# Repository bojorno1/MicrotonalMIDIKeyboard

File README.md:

<h1>Microtonal MIDI Keyboard</h1>

<h2><em>the notes between the notes...</em></h2>
<br>
This is a microtonal MIDI keyboard, made for the Hack Club Half-Life project week 3/8.
<br>
This keyboard adds extra keys for the keys C 1/4#, C 3/4#, D 1/4#, D 3/4#, and so on. This keyboard uses low-profile MX keys as its switches, which are set in a matrix as to save IO on the Waveshare ESP32-S3-Zero. There is also a rotary encoder present on the board for volume control and mute functions. Special keycaps for this board will be 3D-Printable and found in the Keycaps folder in this repository once created. This keyboard uses MIDI 1.0 to transmit the musical data from this keyboard. Please note that the data used for microtones in this keyboard may not be compatible with certain softwares.
<br>
Set up instructions will be available upon firmware completion. 
<h4>Schematics available <a href="https://github.com/bojorno1/MicrotonalMIDIKeyboard/blob/main/pcb/schematic.pdf">here...</a></h4>
<h4>Keycap files available <a href="https://github.com/bojorno1/MicrotonalMIDIKeyboard/tree/main/keycaps">here...</a></h4>
<h4>Firmware available <a href="https://github.com/bojorno1/MicrotonalMIDIKeyboard/tree/main/firmware">here...</a></h4>

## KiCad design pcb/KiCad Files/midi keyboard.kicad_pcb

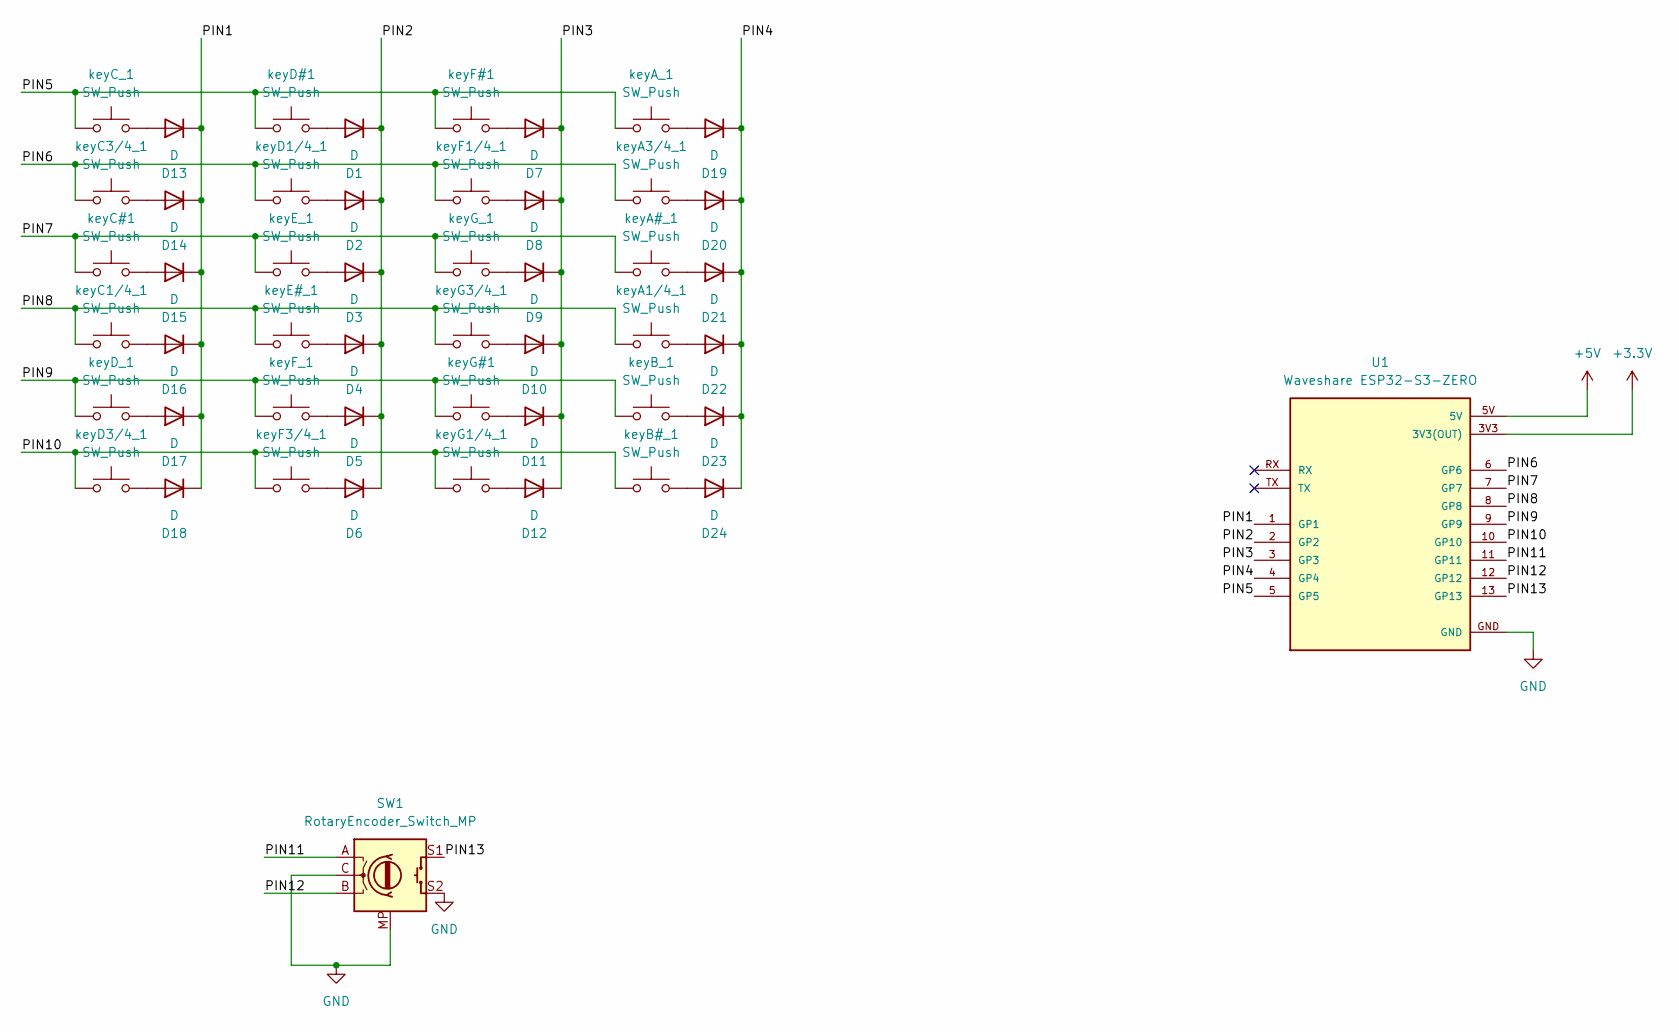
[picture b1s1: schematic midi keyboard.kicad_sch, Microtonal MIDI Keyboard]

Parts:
D1, D2, D3, D4, D5, D6, D7, D8, D9, D10, D11, D12, D13, D14, D15, D16, D17, D18, D19, D20, D21, D22, D23, D24: D; D_DO-15_P10.16mm_Horizontal
SW1: RotaryEncoder_Switch_MP; RotaryEncoder_Alps_EC11E-Switch_Vertical_H20mm
U1: Waveshare ESP32-S3-ZERO; Waveshare ESP32-S3-Zero; PARTREV NA
keyA1/4_1, keyA3/4_1: SW_Push; Kailh Choc Low-Profile Switches
keyA#_1: SW_Push; Kailh Choc Low-Profile Switches
keyA_1: SW_Push; Kailh Choc Low-Profile Switches
keyB#_1: SW_Push; Kailh Choc Low-Profile Switches
keyB_1: SW_Push; Kailh Choc Low-Profile Switches
keyC1/4_1, keyC3/4_1: SW_Push; Kailh Choc Low-Profile Switches
keyC#1: SW_Push; Kailh Choc Low-Profile Switches
keyC_1: SW_Push; Kailh Choc Low-Profile Switches
keyD1/4_1, keyD3/4_1: SW_Push; Kailh Choc Low-Profile Switches
keyD#1: SW_Push; Kailh Choc Low-Profile Switches
keyD_1: SW_Push; Kailh Choc Low-Profile Switches
keyE#_1: SW_Push; Kailh Choc Low-Profile Switches
keyE_1: SW_Push; Kailh Choc Low-Profile Switches
keyF1/4_1, keyF3/4_1: SW_Push; Kailh Choc Low-Profile Switches
keyF#1: SW_Push; Kailh Choc Low-Profile Switches
keyF_1: SW_Push; Kailh Choc Low-Profile Switches
keyG1/4_1, keyG3/4_1: SW_Push; Kailh Choc Low-Profile Switches
keyG#1: SW_Push; Kailh Choc Low-Profile Switches
keyG_1: SW_Push; Kailh Choc Low-Profile Switches

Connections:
+3.3V: U1.3V3 (3V3(OUT))
+5V: U1.5V
/<NO NET>: D13.1 (K), D14.1 (K), D15.1 (K), D16.1 (K), D17.1 (K), D18.1 (K), U1.1 (GP1)
/PIN2: D1.1 (K), D2.1 (K), D3.1 (K), D4.1 (K), D5.1 (K), D6.1 (K), U1.2 (GP2)
/PIN3: D7.1 (K), D8.1 (K), D9.1 (K), D10.1 (K), D11.1 (K), D12.1 (K), U1.3 (GP3)
/PIN4: D19.1 (K), D20.1 (K), D21.1 (K), D22.1 (K), D23.1 (K), D24.1 (K), U1.4 (GP4)
/PIN5: U1.5 (GP5), keyA_1.1, keyC_1.1, keyD#1.1, keyF#1.1
/PIN6: U1.6 (GP6), keyA3/4_1.1, keyC3/4_1.1, keyD1/4_1.1, keyF1/4_1.1
/PIN7: U1.7 (GP7), keyA#_1.1, keyC#1.1, keyE_1.1, keyG_1.1
/PIN8: U1.8 (GP8), keyA1/4_1.1, keyC1/4_1.1, keyE#_1.1, keyG3/4_1.1
/PIN9: U1.9 (GP9), keyB_1.1, keyD_1.1, keyF_1.1, keyG#1.1
/PIN10: U1.10 (GP10), keyB#_1.1, keyD3/4_1.1, keyF3/4_1.1, keyG1/4_1.1
/PIN11: SW1.A, U1.11 (GP11)
/PIN12: SW1.B, U1.12 (GP12)
/PIN13: SW1.S1, U1.13 (GP13)
GND: SW1.C, SW1.MP, SW1.S2, U1.GND
unnamed: D1.2 (A), keyD#1.2
unnamed: D2.2 (A), keyD1/4_1.2
unnamed: D3.2 (A), keyE_1.2
unnamed: D4.2 (A), keyE#_1.2
unnamed: D5.2 (A), keyF_1.2
unnamed: D6.2 (A), keyF3/4_1.2
unnamed: D7.2 (A), keyF#1.2
unnamed: D8.2 (A), keyF1/4_1.2
unnamed: D9.2 (A), keyG_1.2
unnamed: D10.2 (A), keyG3/4_1.2
unnamed: D11.2 (A), keyG#1.2
unnamed: D12.2 (A), keyG1/4_1.2
unnamed: D13.2 (A), keyC_1.2
unnamed: D14.2 (A), keyC3/4_1.2
unnamed: D15.2 (A), keyC#1.2
unnamed: D16.2 (A), keyC1/4_1.2
unnamed: D17.2 (A), keyD_1.2
unnamed: D18.2 (A), keyD3/4_1.2
unnamed: D19.2 (A), keyA_1.2
unnamed: D20.2 (A), keyA3/4_1.2
unnamed: D21.2 (A), keyA#_1.2
unnamed: D22.2 (A), keyA1/4_1.2
unnamed: D23.2 (A), keyB_1.2
unnamed: D24.2 (A), keyB#_1.2

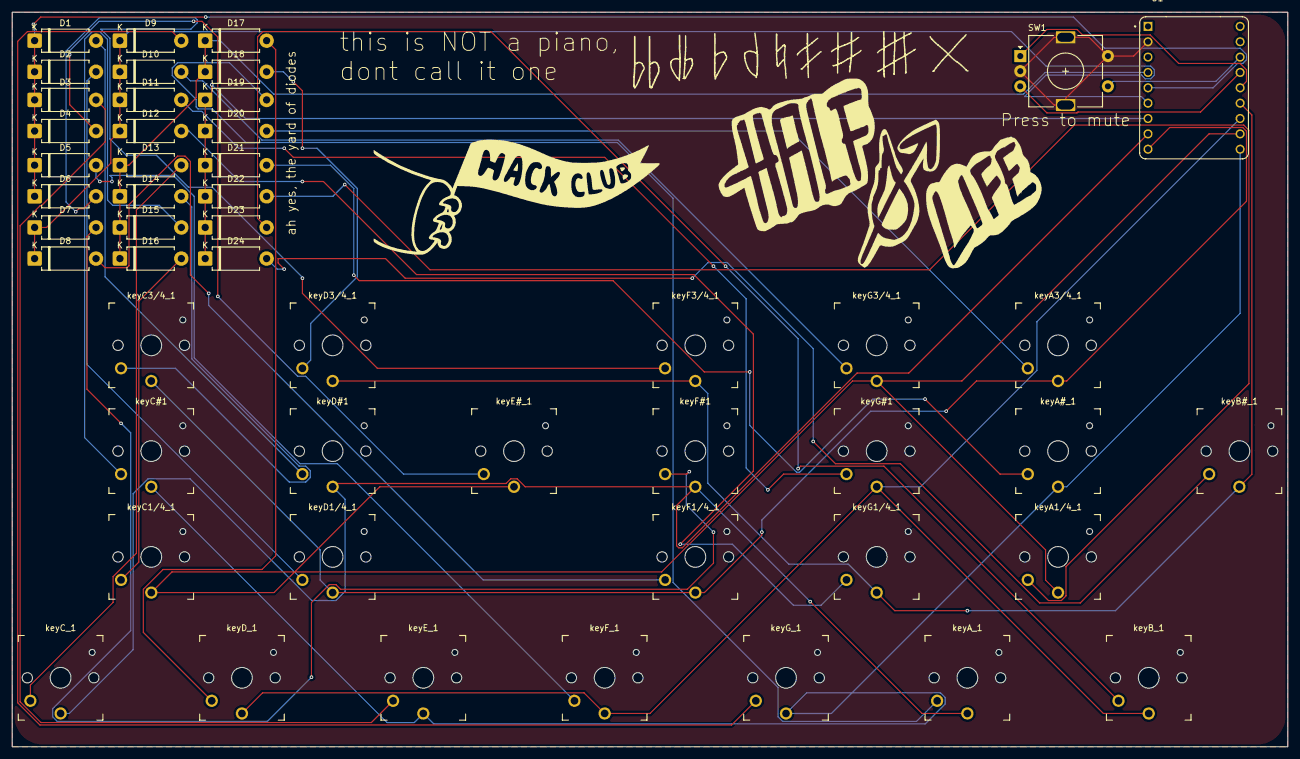
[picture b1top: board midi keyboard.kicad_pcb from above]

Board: 2 copper layers, 211.0 x 121.5 mm, 50 parts (0 on the bottom side), 38 nets.

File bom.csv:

Designator,Footprint,Quantity,Value,LCSC Part #
"D1, D10, D11, D12, D13, D14, D15, D16, D17, D18, D19, D2, D20, D21, D22, D23, D24, D3, D4, D5, D6, D7, D8, D9",D_DO-15_P10.16mm_Horizontal,24,D,
"KEYA#_1, KEYA1/4_1, KEYA3/4_1, KEYA_1, KEYB#_1, KEYB_1, KEYC#1, KEYC1/4_1, KEYC3/4_1, KEYC_1, KEYD#1, KEYD1/4_1, KEYD3/4_1, KEYD_1, KEYE#_1, KEYE_1, KEYF#1, KEYF1/4_1, KEYF3/4_1, KEYF_1, KEYG#1, KEYG1/4_1, KEYG3/4_1, KEYG_1",Kailh Choc Low-Profile Switches,24,SW_Push,
SW1,RotaryEncoder_Alps_EC11E-Switch_Vertical_H20mm,1,RotaryEncoder_Switch_MP,
U1,Waveshare ESP32-S3-Zero,1,Waveshare ESP32-S3-ZERO,
